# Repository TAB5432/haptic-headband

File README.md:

# haptic-headband
A haptic headband that uses sensory indicators (buzzers) to help guide people and also alert them when obstacles are nearby.

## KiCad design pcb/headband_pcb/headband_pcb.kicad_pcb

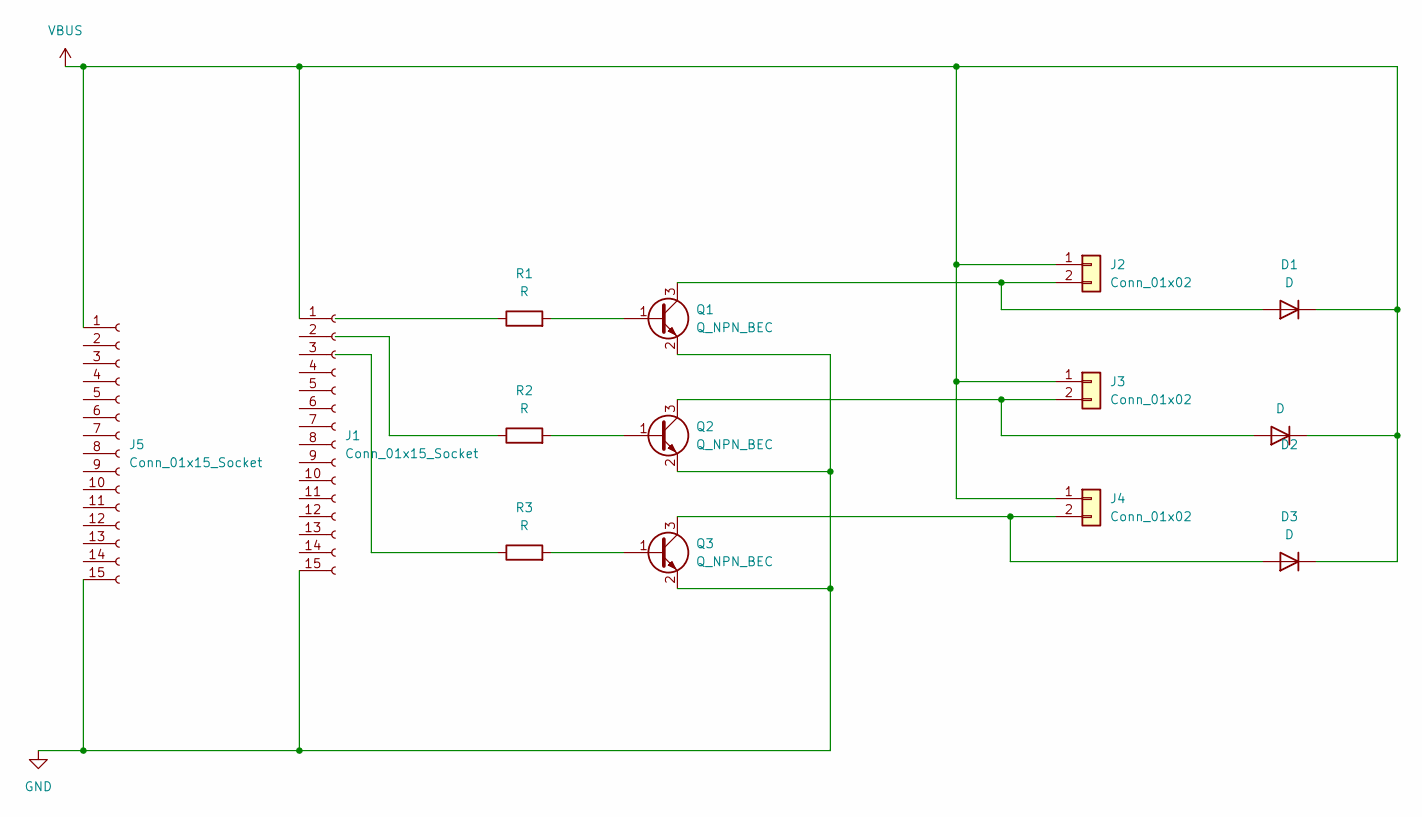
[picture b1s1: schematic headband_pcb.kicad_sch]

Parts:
D1, D2, D3: D; D_0805_2012Metric
J1, J5: Conn_01x15_Socket; PinSocket_1x15_P2.54mm_Vertical
J2, J3, J4: Conn_01x02; JST_PH_B2B-PH-K_1x02_P2.00mm_Vertical
Q1, Q2, Q3: Q_NPN_BEC; SOT-23-3
R1, R2, R3: R; R_0805_2012Metric

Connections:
GND: J1.15, J5.15, Q1.2 (E), Q2.2 (E), Q3.2 (E)
unnamed: D1.2 (A), J2.2, Q1.3 (C)
unnamed: D2.2 (A), J3.2, Q2.3 (C)
unnamed: D3.2 (A), J4.2, Q3.3 (C)
unnamed: Q1.1 (B), R1.2
unnamed: Q2.1 (B), R2.2
unnamed: Q3.1 (B), R3.2
VBUS: D1.1 (K), D2.1 (K), D3.1 (K), J1.1, J2.1, J3.1, J4.1, J5.1

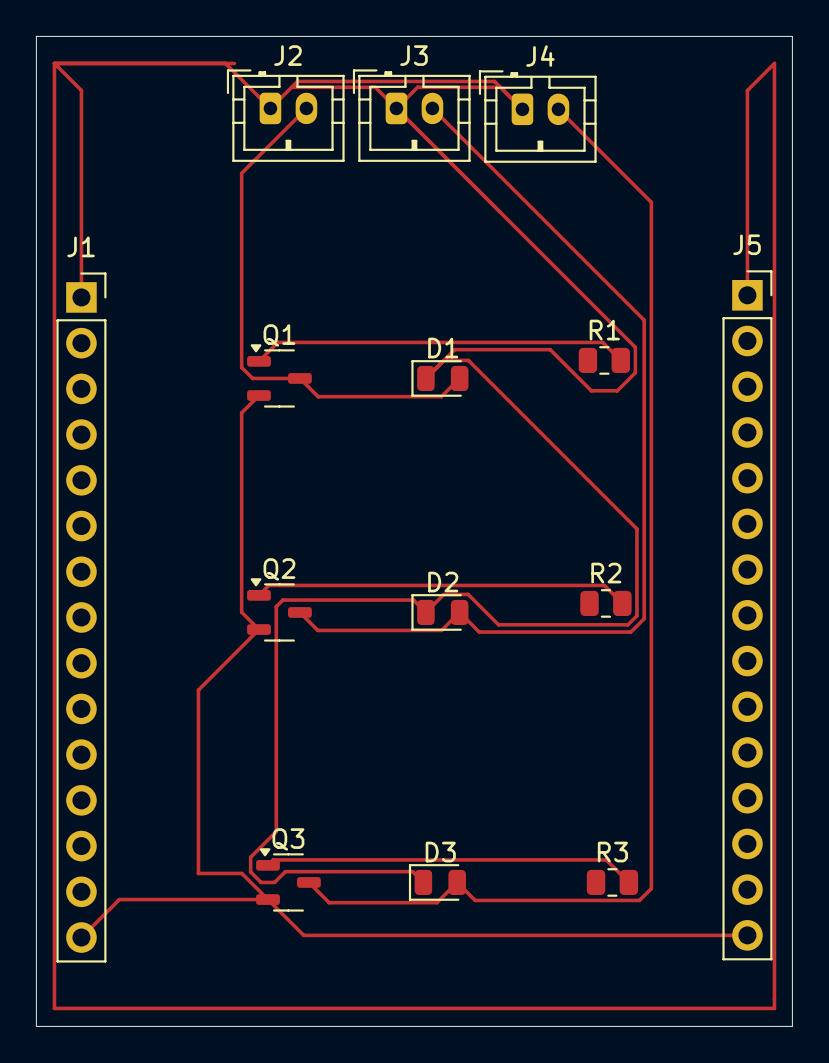
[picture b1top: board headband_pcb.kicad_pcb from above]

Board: 2 copper layers, 42.0 x 55.0 mm, 14 parts (0 on the bottom side), 8 nets.
